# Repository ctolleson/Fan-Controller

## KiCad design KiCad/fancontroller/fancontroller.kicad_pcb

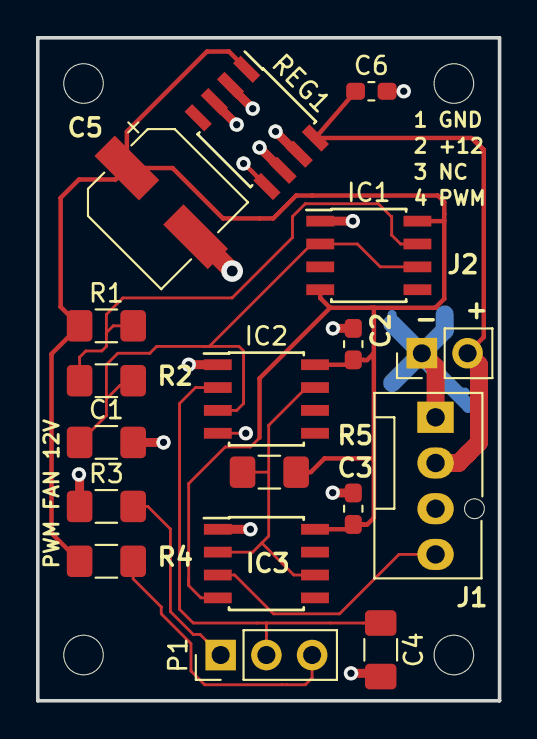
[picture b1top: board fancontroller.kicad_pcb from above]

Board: 2 copper layers, 25.7 x 36.8 mm, 22 parts (0 on the bottom side), 10 nets.

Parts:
C1: 560pF; C_1206_3216Metric_Pad1.42x1.75mm_HandSolder
C2, C3, C6: 100nF; C_0603_1608Metric_Pad1.05x0.95mm_HandSolder
C4: 100pF; C_1206_3216Metric_Pad1.42x1.75mm_HandSolder
C5: 47uF 35V; CP_Elec_6.3x5.8
H1, H2, H3, H4: M2 mounting hole; MountingHole_2.2mm_M2
IC1, IC3: NE555DR; SOIC-8_3.9x4.9mm_P1.27mm
IC2: LM311DR; SOIC-8_3.9x4.9mm_P1.27mm
J1: Fan 4-pin; FanPinHeader_1x04_P2.54mm_Vertical
J2: Power input; PinHeader_1x02_P2.54mm_Vertical
P1: 10k; PinHeader_1x03_P2.54mm_Vertical
R1: 10k; R_1206_3216Metric_Pad1.42x1.75mm_HandSolder
R2: 47k; R_1206_3216Metric_Pad1.42x1.75mm_HandSolder
R3, R4: 9.1k; R_1206_3216Metric_Pad1.42x1.75mm_HandSolder
R5: 1k; R_1206_3216Metric_Pad1.42x1.75mm_HandSolder
REG1: KF50BD-TR; SOIC-8_3.9x4.9mm_P1.27mm

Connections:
+5V: C2.2, C3.1, C5.1, IC1.4, IC1.8, IC2.8, IC3.4, IC3.8, R1.1, R4.1, R5.2, REG1.1
+12V: C6.1, J1.2, J2.2, REG1.8
COMPARATOR: IC2.7, IC3.2, IC3.6, R5.1
DISCHARGE: IC1.7, R1.2, R2.1
DUTY_REF: C4.1, IC2.2, P1.2
GND: C1.2, C2.1, C3.2, C4.2, C5.2, C6.2, IC1.1, IC2.1, IC2.4, IC3.1, J1.1, J2.1, R3.1, REG1.2, REG1.3, REG1.5, REG1.6, REG1.7
POT_HIGH: P1.3, R4.2
POT_LOW: P1.1, R3.2
PWM_OUT: IC3.3, J1.4
RAMP: C1.1, IC1.2, IC1.6, IC2.3, R2.2

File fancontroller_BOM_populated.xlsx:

References | Qty/board | Value / description | Original or candidate MPN | Manufacturer | KiCad footprint | LCSC code | Assembly | Match status | Review note | Source URL
REG1 | 1 | 5 V, 500 mA LDO regulator | KF50BD-TR | STMicroelectronics | Recovered2018:SOIC-8_3.9x4.9mm_P1.27mm | C222151 | SMT | Stocked quote replacement; 12 V only | Same pinout and active-low inhibit. 500 mA; input limit 20 V. Original 12-28 V 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 | https://www.st.com/resource/en/datasheet/kfxx.pdf
C1 | 1 | 560 pF ceramic capacitor | CC1206JRNPO9BN561 | Yageo | Recovered2018:C_1206_3216Metric_Pad1.42x1.75mm_HandSolder | C577166 | SMT | Stocked quote replacement | 560 pF, 50 V, NP0, 5%, 1206. Replaces original 10% X7R timing capacitor. | https://jlcpcb.com/partdetail/YAGEO-CC1206JRNPO9BN561/C577166
C2, C3 | 2 | 100 nF ceramic capacitor | C0603C104K3RALTU | KEMET | Recovered2018:C_0603_1608Metric_Pad1.05x0.95mm_HandSolder | C2167748 | SMT | Exact MPN; verify stock | Original BOM suggested this part for both reference designators. | https://www.lcsc.com/product-detail/C2167748.html
C4 | 1 | 100 pF ceramic capacitor | CC1206JRNPOBBN101 | Yageo | Recovered2018:C_1206_3216Metric_Pad1.42x1.75mm_HandSolder | C113888 | SMT | Stocked quote replacement | 100 pF, 500 V, NP0, 5%, 1206. Retains capacitance, voltage rating and package. | https://jlcpcb.com/partdetail/YAGEO-CC1206JRNPOBBN101/C113888
C5 | 1 | 47 µF, 35 V polarized aluminum capacitor | EEEFK1V470AP | Panasonic | Recovered2018:CP_Elec_6.3x5.8 | C336786 | SMT | Stocked quote replacement | Same 6.3x5.8 mm case; 0.36 ohm impedance. Rated 2000 h at 105 C versus original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 | https://industrial.panasonic.com/ww/products/pt/aluminum-cap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
IC1, IC3 | 2 | 555 timer, SOIC-8 | NE555DR | Texas Instruments | Recovered2018:SOIC-8_3.9x4.9mm_P1.27mm | C7593 | SMT | Exact MPN; verify stock | Two devices shown in both schematic image and BOM. | https://www.lcsc.com/product-detail/C7593.html
IC2 | 1 | Comparator, SOIC-8 | LM311DR | Texas Instruments | Recovered2018:SOIC-8_3.9x4.9mm_P1.27mm | C12597 | SMT | Exact MPN; verify stock | Pin mapping and supply wiring still need reconstruction. | https://www.lcsc.com/product-detail/C12597.html
R1 | 1 | 10 kΩ, 1%, 1206 resistor | RC1206FR-0710KL | Yageo | Recovered2018:R_1206_3216Metric_Pad1.42x1.75mm_HandSolder | C132649 | SMT | Exact MPN; verify stock | Original BOM test-circuit part. | https://www.lcsc.com/product-detail/C132649.html
R2 | 1 | 47 kΩ, 1%, 1206 resistor | RC1206FR-0747KL | Yageo | Recovered2018:R_1206_3216Metric_Pad1.42x1.75mm_HandSolder | C137270 | SMT | Exact MPN; verify stock | Original BOM test-circuit part. | https://www.lcsc.com/product-detail/C137270.html
R3, R4 | 2 | 9.1 kΩ, 1%, 1206 resistor | RC1206FR-079K1L | Yageo | Recovered2018:R_1206_3216Metric_Pad1.42x1.75mm_HandSolder | C163368 | SMT | Exact MPN matched to JLCPCB | Original BOM test-circuit part; obtain a current JLC/LCSC listing. | https://jlcpcb.com/partdetail/YAGEO-RC1206FR079K1L/C163368
R5 | 1 | 1 kΩ, 1%, 1206 resistor | RC1206FR-071KL | Yageo | Recovered2018:R_1206_3216Metric_Pad1.42x1.75mm_HandSolder | C131398 | SMT | Exact MPN; verify stock | Original BOM test-circuit part. | https://www.lcsc.com/product-detail/C131398.html
P1 | 1 | 10 kΩ potentiometer | PDF241-S425F-103B0 | Bourns |  | C6626952 | Through-hole / manual | Candidate; footprint open | Original BOM recommendation. Confirm pin spacing, shaft orientation, enclosure 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 | https://lcsc.com/product-detail/Potentiometers-Variable-Resi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
J1 | 1 | 4-pin PWM fan header, 2.54 mm | 0470531000 | Molex |  |  | Through-hole / manual | MPN known; footprint open | Original BOM lists header. Confirm orientation and board mounting geometry. | https://www.molex.com/pdm_docs/sd/470531000_sd.pdf
J2 | 1 | 2-pin power input connector |  |  |  |  | Through-hole / manual | Part selection required | Inferred from the board image; omitted from the original BOM. Confirm pitch, po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
